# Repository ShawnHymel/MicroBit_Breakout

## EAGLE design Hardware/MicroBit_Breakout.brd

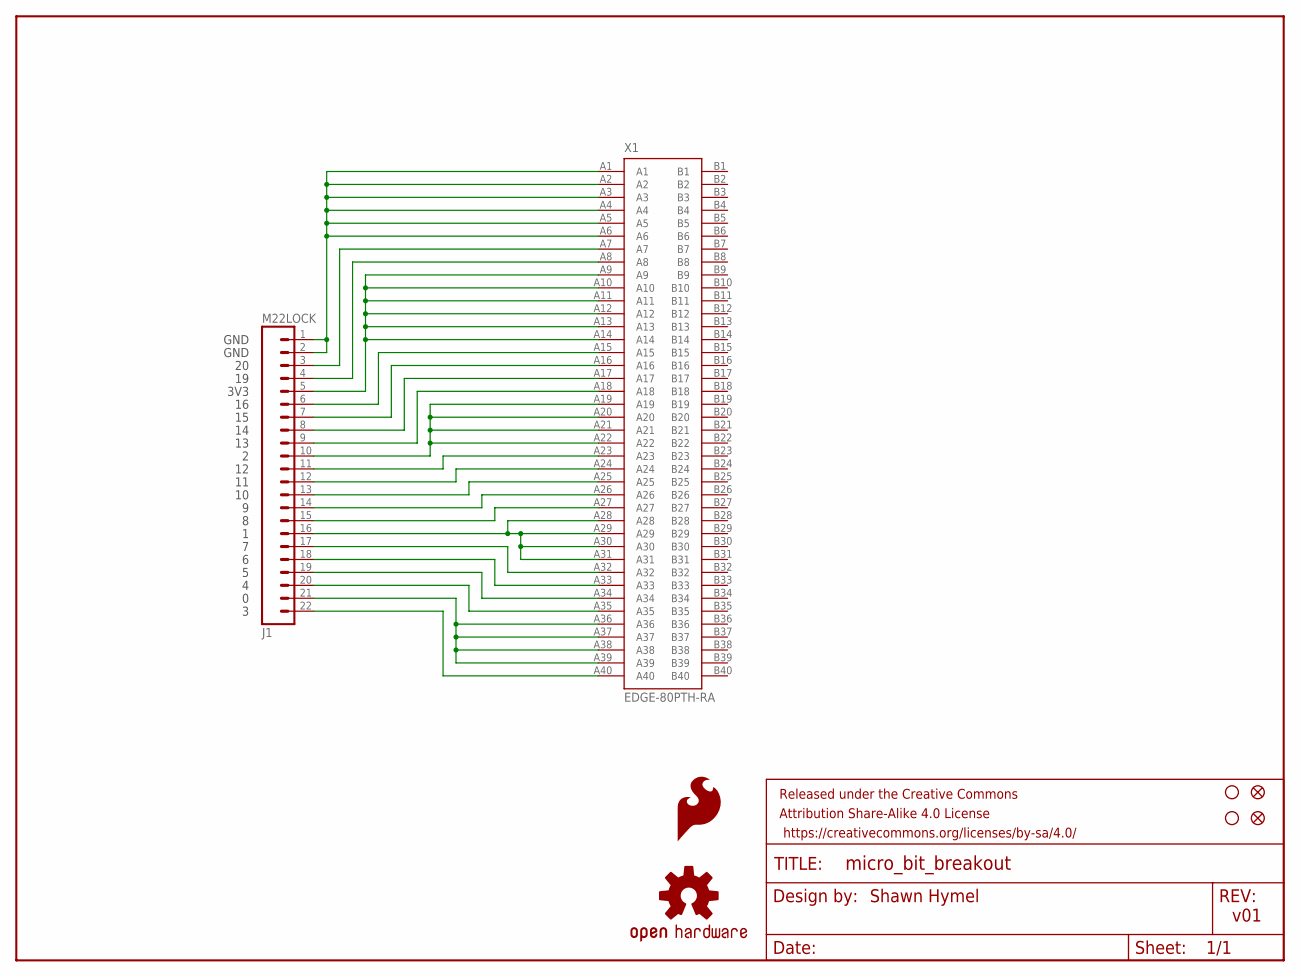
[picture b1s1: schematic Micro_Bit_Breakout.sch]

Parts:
FD1, FD2: FIDUCIAL1X2; FIDUCIAL-1X2
FRAME1: FRAME-LETTER; CREATIVE_COMMONS
H1, H2: STAND-OFF
J1: M22LOCK; 1X22_LOCK
LOGO1: SFE_LOGO_FLAME.1_INCH; SFE_LOGO_FLAME_.1
LOGO3: OSHW-LOGOS; OSHW-LOGO-S
X1: EDGE-80PTH-RA; VEC-127-080-R

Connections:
GND: J1.1, J1.2, X1.A1, X1.A2, X1.A3, X1.A4, X1.A5, X1.A6
unnamed: J1.6, X1.A15
unnamed: J1.3, X1.A7
unnamed: J1.4, X1.A8
unnamed: J1.5, X1.A9, X1.A10, X1.A11, X1.A12, X1.A13, X1.A14
unnamed: J1.7, X1.A16
unnamed: J1.8, X1.A17
unnamed: J1.9, X1.A18
unnamed: J1.10, X1.A19, X1.A20, X1.A21, X1.A22
unnamed: J1.11, X1.A23
unnamed: J1.12, X1.A24
unnamed: J1.13, X1.A25
unnamed: J1.14, X1.A26
unnamed: J1.15, X1.A27
unnamed: J1.16, X1.A28, X1.A29, X1.A30, X1.A31
unnamed: J1.17, X1.A32
unnamed: J1.18, X1.A33
unnamed: J1.19, X1.A34
unnamed: J1.20, X1.A35
unnamed: J1.21, X1.A36, X1.A37, X1.A38, X1.A39
unnamed: J1.22, X1.A40

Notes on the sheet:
Shawn Hymel
v01
GND
3V3

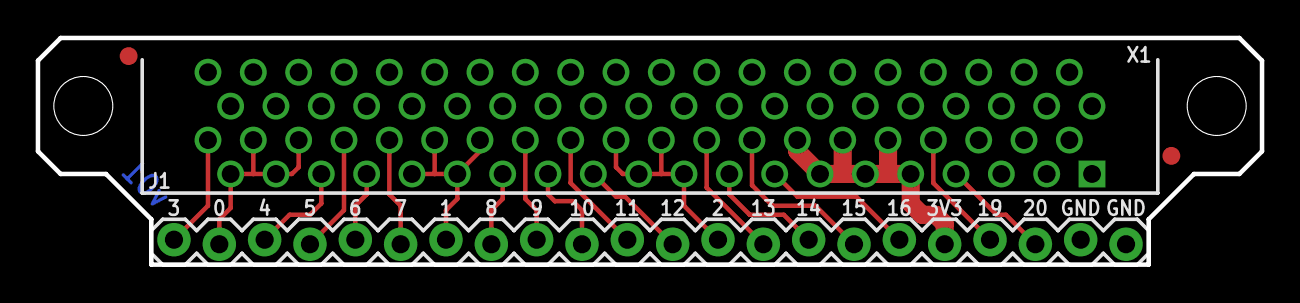
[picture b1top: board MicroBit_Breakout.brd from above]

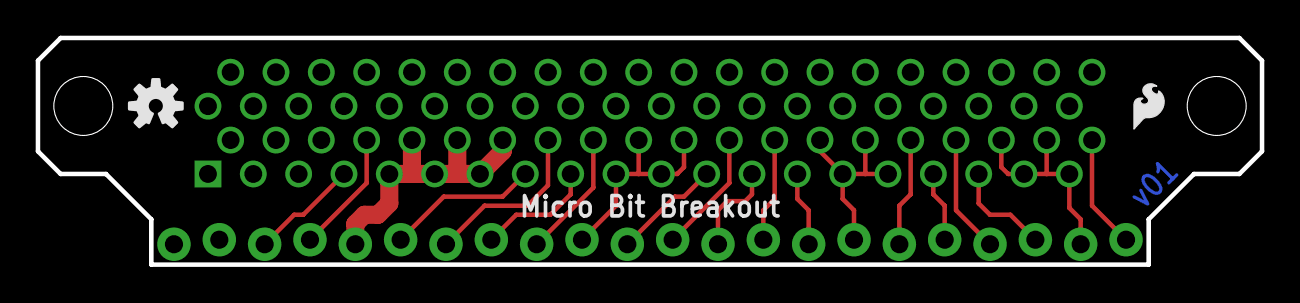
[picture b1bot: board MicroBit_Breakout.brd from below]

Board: 2 copper layers, 68.6 x 12.7 mm, 9 parts (2 on the bottom side), 21 nets.

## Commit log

2016-05-30 Basic schematic and layout done.
2016-05-30 Layout complete
2016-05-30 Changed sch and brd files to match repo name. Added ignore file.

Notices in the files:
parts and their libraries:
SparkFun-Aesthetics: Licensing: Creative Commons ShareAlike 4.0 International - https://creativecommons.org/licenses/by-sa/4.0
SparkFun-Aesthetics: Released under the Creative Commons Attribution Share-Alike 4.0 License
SparkFun-Aesthetics: https://creativecommons.org/licenses/by-sa/4.0
